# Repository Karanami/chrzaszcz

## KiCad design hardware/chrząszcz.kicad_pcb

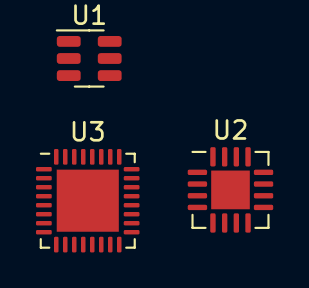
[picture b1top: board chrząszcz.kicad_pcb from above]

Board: 4 copper layers, 3 parts (0 on the bottom side), 4 nets, no tracks yet.

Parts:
U1: AP9101CK6; SOT-23-6
U2: LTC4055; QFN-16-1EP_4x4mm_P0.65mm_EP2.15x2.15mm
U3: STM32G4A1KEUx; QFN-32-1EP_5x5mm_P0.5mm_EP3.45x3.45mm

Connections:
+2V8: U3.1 (VDD), U3.17 (VDD)
GND: U3.14 (VSSA), U3.16 (VSS), U3.32 (VSS), U3.33 (VSS)
unnamed: U2.10 (GND), U2.17 (GND)
unnamed: U2.1 (IN), U2.4 (IN)

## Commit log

2023-04-21 inti commit
